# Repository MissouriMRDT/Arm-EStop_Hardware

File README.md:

# Arm-EStop_Hardware
a generic E-Stop that can be used to E-Stop any power supply

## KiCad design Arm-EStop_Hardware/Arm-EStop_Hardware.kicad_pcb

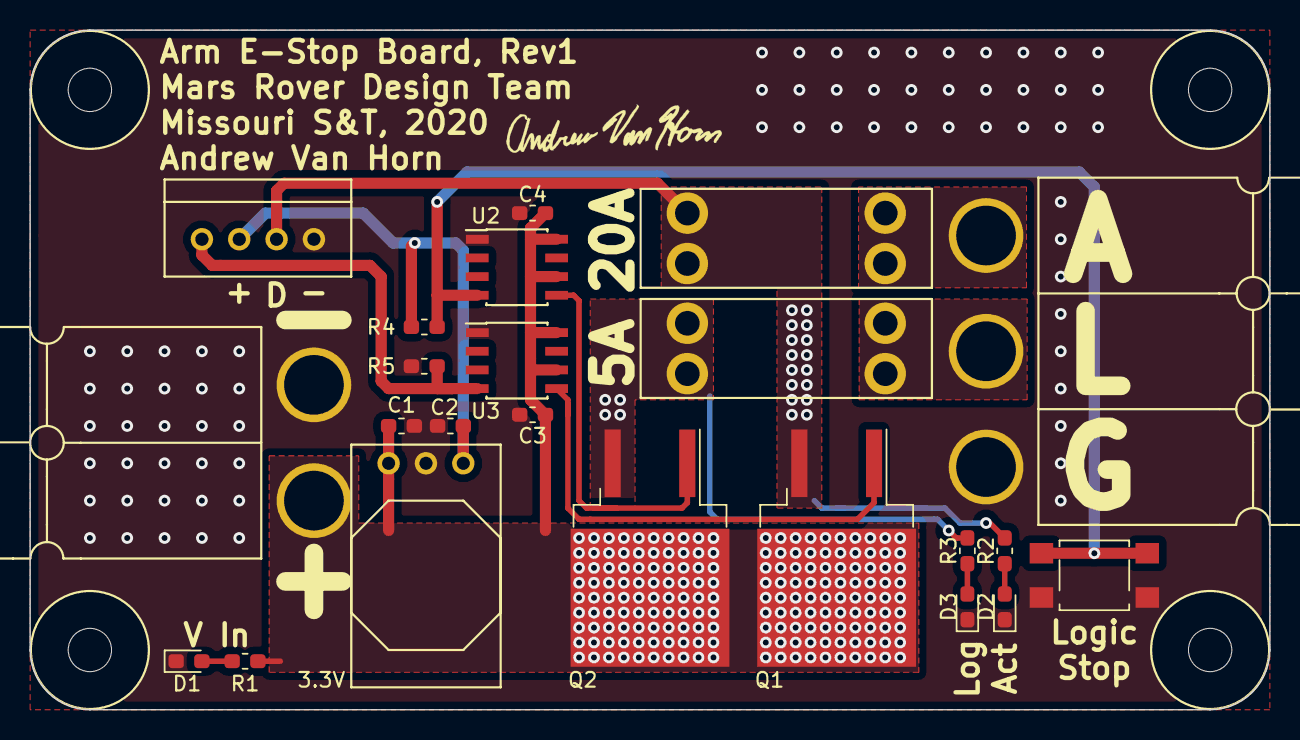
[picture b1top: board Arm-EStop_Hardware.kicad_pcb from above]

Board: 2 copper layers, 84.3 x 46.2 mm, 23 parts (0 on the bottom side), 14 nets.

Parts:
C1, C2, C3, C4: 10u; C_0603_1608Metric_Pad1.05x0.95mm_HandSolder
Conn1: AndersonPP; Anderson_2_Horizontal_Side_by_Side
Conn2: AndersonPP; Anderson_3_Horizontal_Side_by_Side
D1, D2, D3: Green; D_0603_1608Metric_Pad1.05x0.95mm_HandSolder
F1: 20A; ATC_Fuse_Block
F2: 5A; ATC_Fuse_Block
Logic: SW_Push_Open; SW_SPST_TL3305A
Q1, Q2: IRFS7437TRLPBFCT; TO-263-2
R1, R2, R3: 1K; R_0603_1608Metric_Pad1.05x0.95mm_HandSolder
R4, R5: 10k; R_0603_1608Metric_Pad1.05x0.95mm_HandSolder
U1: 3.3V; OKI_Horizontal
U2, U3: LT1910; SOIC-8_3.9x4.9mm_P1.27mm
U5: E_STOP+LED; MOLEX_SL_04_Vertical

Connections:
+3V3: C2.1, R4.1, U1.3, U5.2
+12L: F2.2, Q2.3, R3.1
+12V: C1.1, C3.1, C4.1, Conn1.2, Q1.2, Q2.2, R1.1, U1.1, U2.6, U2.8, U3.6, U3.8
+12VA: F1.2, Q1.3, R2.1, U5.3
GND: C1.2, C2.2, C3.2, C4.2, Conn1.1, Conn2.1, D1.1, D2.1, D3.1, Logic.2, R5.2, U1.2, U2.1, U3.1, U5.4
unnamed: Conn2.2, F2.1
unnamed: Conn2.3, F1.1
unnamed: D1.2, R1.2
unnamed: D2.2, R2.2
unnamed: D3.2, R3.2
unnamed: Logic.1, R4.2, U2.4
unnamed: R5.1, U3.4, U5.1
V_Act_Gate: Q1.1, U3.5
V_Log_Gate: Q2.1, U2.5

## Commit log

2019-09-26 created schematic
2019-10-29 polished schematic
2019-10-29 Changed FET part number
2019-11-02 swapped MOSFETs, annotated and assigned footprints
2019-11-02 started layout
2019-11-03 high level placement
2019-12-03 finished layout
2019-12-03 switched logic pushbutton to be NO
2019-12-13 Final changes before PRR
2019-12-13 created gerbs
2019-12-14 Created BOM
